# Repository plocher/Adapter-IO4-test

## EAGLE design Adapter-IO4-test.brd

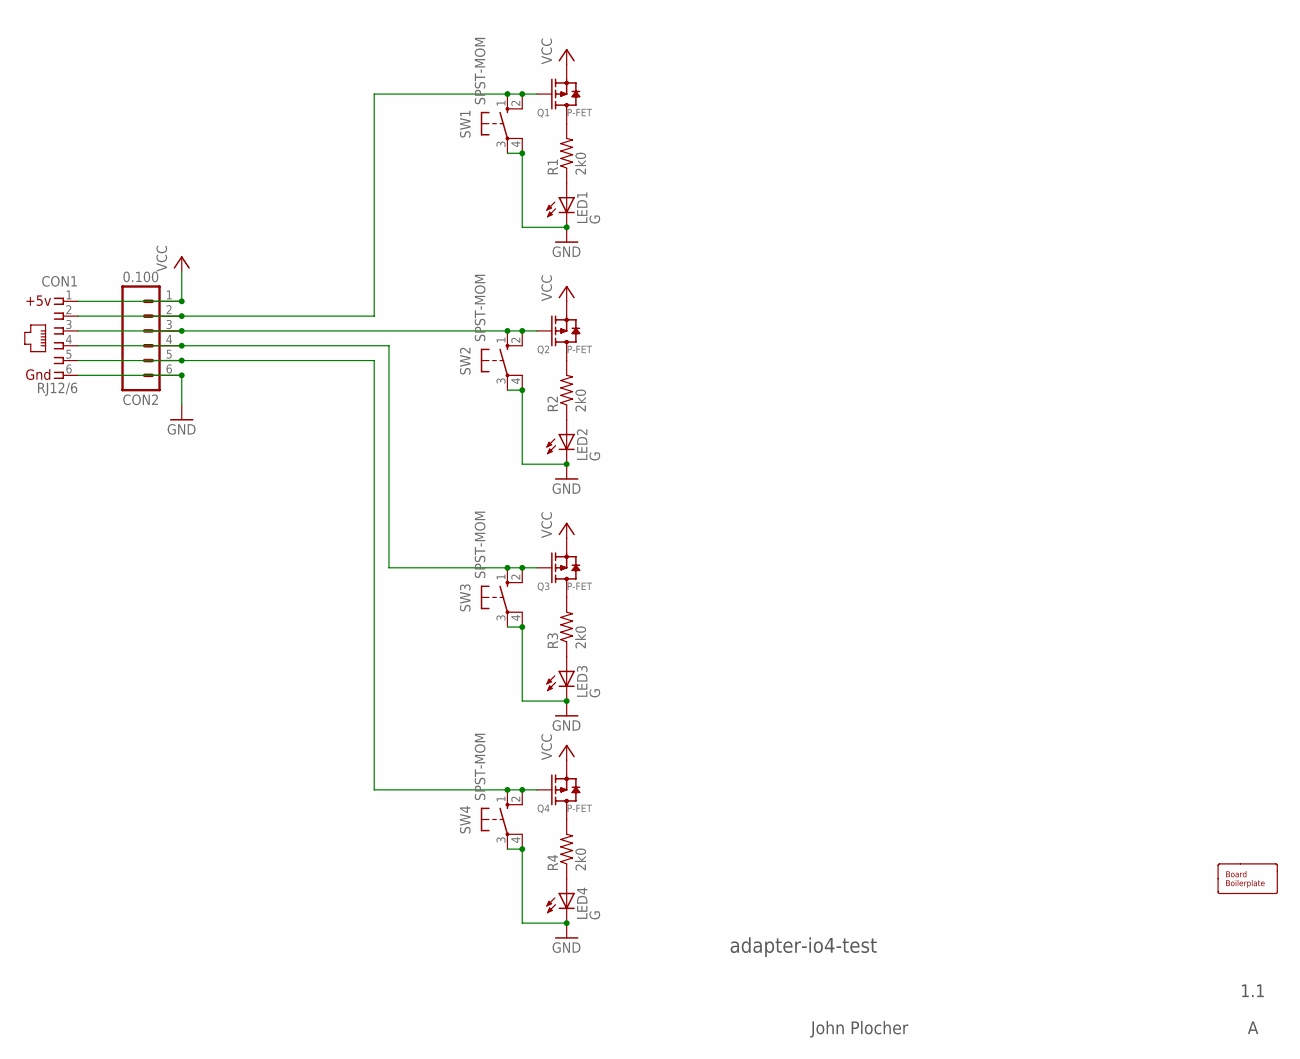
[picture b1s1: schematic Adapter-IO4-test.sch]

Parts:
BOARD1: BOARD50X50-NOHOLES; BOARD-SEEED5X5-NOHOLES
CON1: RJ12/6; RJ25-INVERTED
CON2: 0.100; 1X06_LOCK
LED1, LED2, LED3, LED4: G; 0603-LED
Q1, Q2, Q3, Q4: P-FET; SOT23-3
R1, R2, R3, R4: 2k0; 0603-RES
SW1, SW2, SW3, SW4: SPST-MOM; B3F-10XX

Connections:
GND: CON1.6, CON2.6, LED1.C, LED2.C, LED3.C, LED4.C, SW1.3, SW1.4 (P1), SW2.3, SW2.4 (P1), SW3.3, SW3.4 (P1), SW4.3, SW4.4 (P1)
unnamed: Q1.3 (D), R1.2
unnamed: LED1.A, R1.1
unnamed: Q2.3 (D), R2.2
unnamed: LED2.A, R2.1
unnamed: Q3.3 (D), R3.2
unnamed: LED3.A, R3.1
unnamed: CON1.2, CON2.2, Q1.1 (G), SW1.1 (S), SW1.2 (S1)
unnamed: CON1.3, CON2.3, Q2.1 (G), SW2.1 (S), SW2.2 (S1)
unnamed: CON1.4, CON2.4, Q3.1 (G), SW3.1 (S), SW3.2 (S1)
unnamed: CON1.5, CON2.5, Q4.1 (G), SW4.1 (S), SW4.2 (S1)
unnamed: Q4.3 (D), R4.2
unnamed: LED4.A, R4.1
VCC: CON1.1, CON2.1, Q1.2 (S), Q2.2 (S), Q3.2 (S), Q4.2 (S)

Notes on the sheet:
1.1
John Plocher

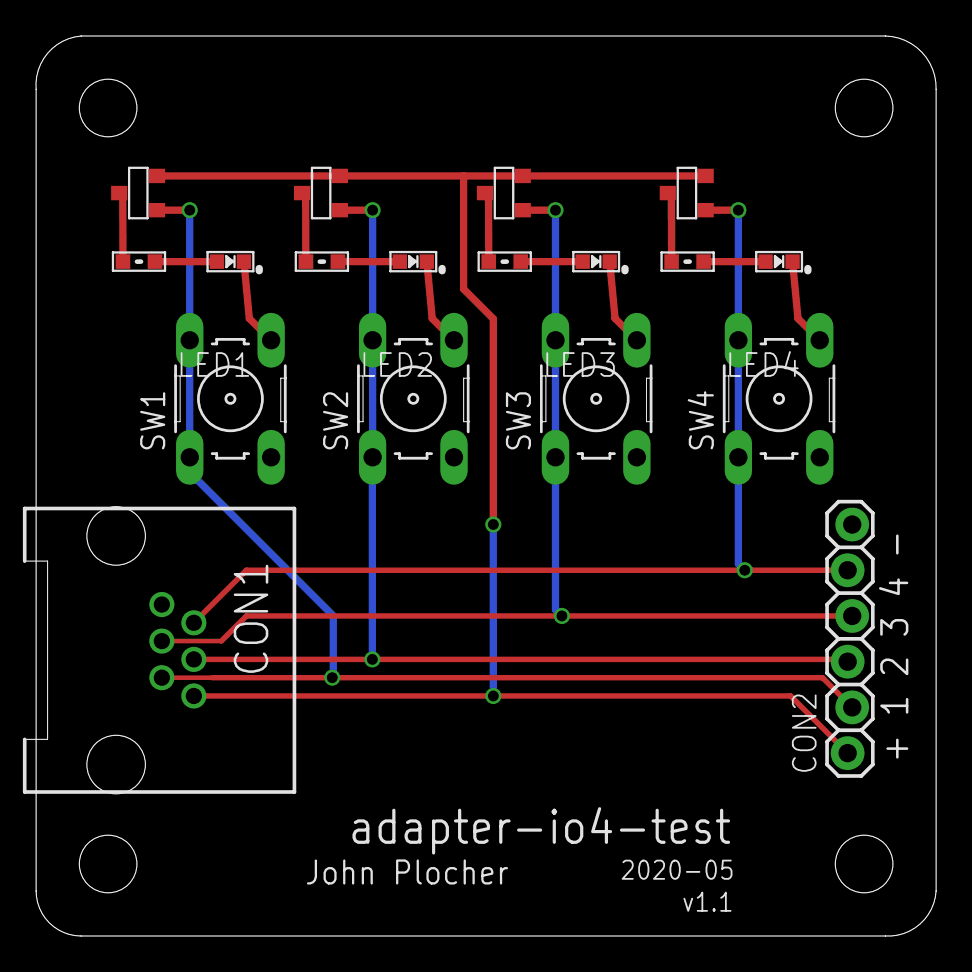
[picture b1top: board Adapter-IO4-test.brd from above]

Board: 2 copper layers, 50.0 x 50.0 mm, 19 parts (0 on the bottom side), 14 nets.

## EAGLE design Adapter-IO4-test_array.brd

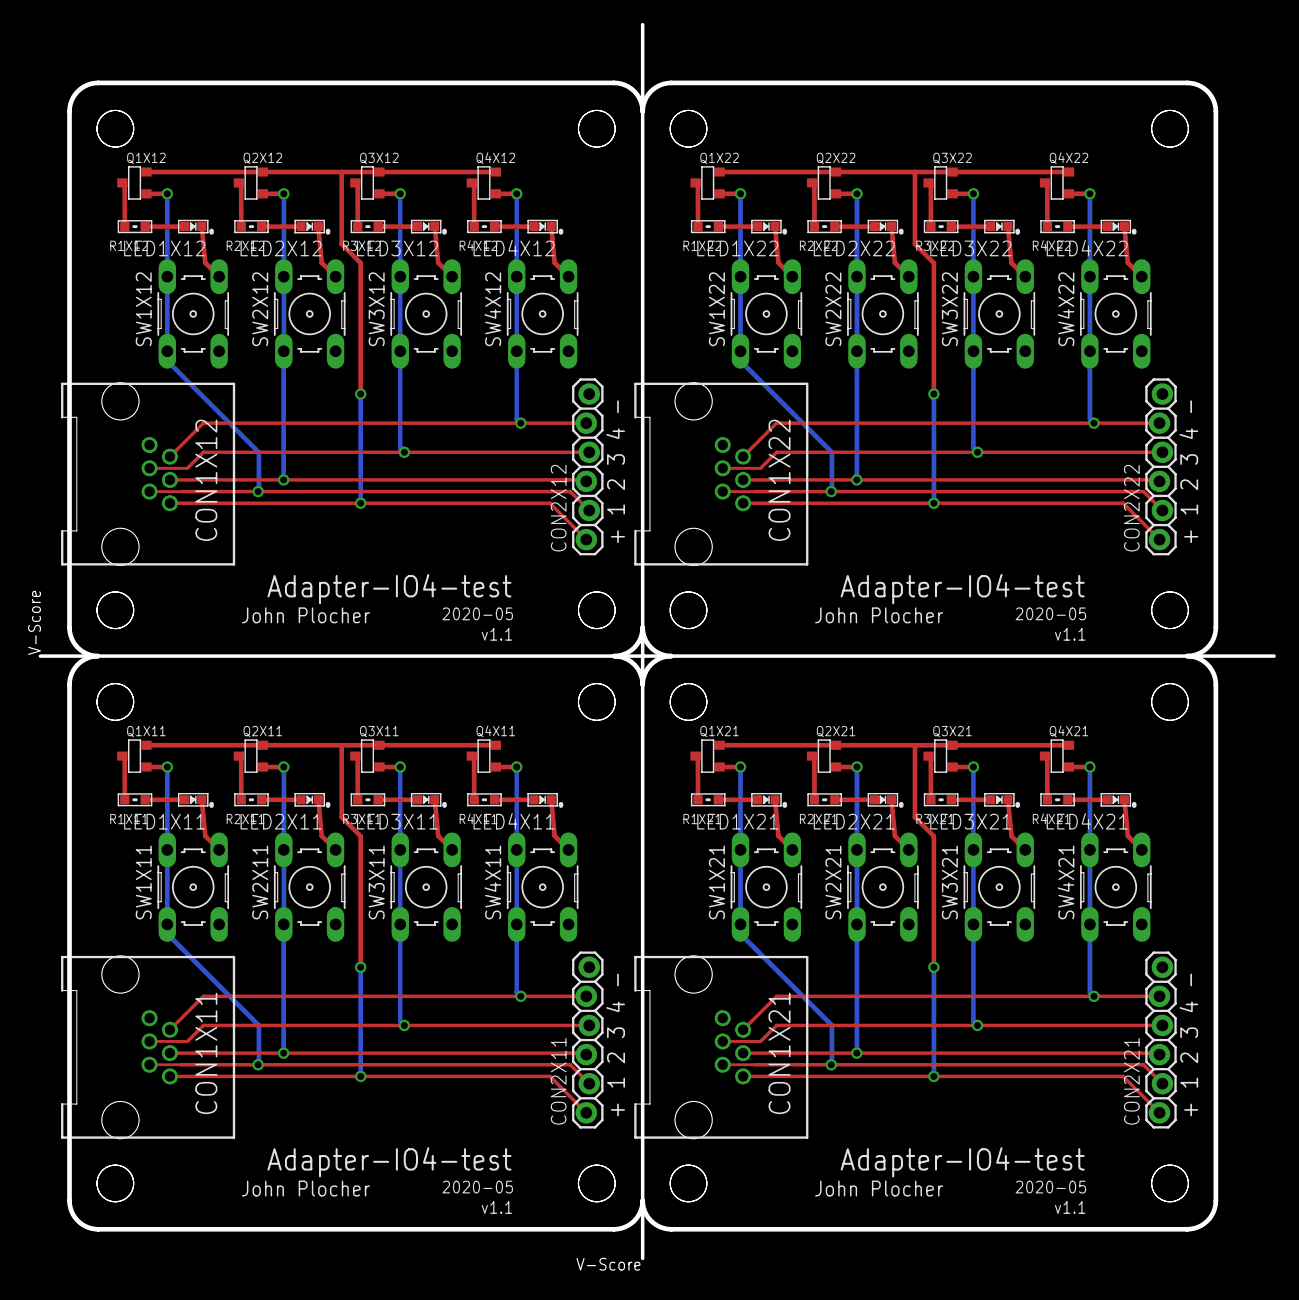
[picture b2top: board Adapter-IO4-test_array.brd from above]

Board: 2 copper layers, 108.9 x 109.0 mm, 72 parts (0 on the bottom side), 56 nets.

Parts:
CON1X11, CON1X12, CON1X21, CON1X22: RJ12/6; RJ25-INVERTED
CON2X11, CON2X12, CON2X21, CON2X22: 0.100; 1X06_LOCK
LED1X11, LED1X12, LED1X21, LED1X22, LED2X11, LED2X12, LED2X21, LED2X22, LED3X11, LED3X12, LED3X21, LED3X22, LED4X11, LED4X12, LED4X21, LED4X22: G; 0603-LED
Q1X11, Q1X12, Q1X21, Q1X22, Q2X11, Q2X12, Q2X21, Q2X22, Q3X11, Q3X12, Q3X21, Q3X22, Q4X11, Q4X12, Q4X21, Q4X22: p-fet; SOT23-3
R1X11, R1X12, R1X21, R1X22, R2X11, R2X12, R2X21, R2X22, R3X11, R3X12, R3X21, R3X22, R4X11, R4X12, R4X21, R4X22: 2k0; 0603-RES
SW1X11, SW1X12, SW1X21, SW1X22, SW2X11, SW2X12, SW2X21, SW2X22, SW3X11, SW3X12, SW3X21, SW3X22, SW4X11, SW4X12, SW4X21, SW4X22: SPST-MOM; B3F-10XX

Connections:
GNDX11: CON1X11.6, CON2X11.6, LED1X11.C, LED2X11.C, LED3X11.C, LED4X11.C, SW1X11.3, SW1X11.4, SW2X11.3, SW2X11.4, SW3X11.3, SW3X11.4, SW4X11.3, SW4X11.4
GNDX12: CON1X12.6, CON2X12.6, LED1X12.C, LED2X12.C, LED3X12.C, LED4X12.C, SW1X12.3, SW1X12.4, SW2X12.3, SW2X12.4, SW3X12.3, SW3X12.4, SW4X12.3, SW4X12.4
GNDX21: CON1X21.6, CON2X21.6, LED1X21.C, LED2X21.C, LED3X21.C, LED4X21.C, SW1X21.3, SW1X21.4, SW2X21.3, SW2X21.4, SW3X21.3, SW3X21.4, SW4X21.3, SW4X21.4
GNDX22: CON1X22.6, CON2X22.6, LED1X22.C, LED2X22.C, LED3X22.C, LED4X22.C, SW1X22.3, SW1X22.4, SW2X22.3, SW2X22.4, SW3X22.3, SW3X22.4, SW4X22.3, SW4X22.4
unnamed: Q1X11.3, R1X11.2
unnamed: Q1X12.3, R1X12.2
unnamed: Q1X21.3, R1X21.2
unnamed: Q1X22.3, R1X22.2
unnamed: LED1X11.A, R1X11.1
unnamed: LED1X12.A, R1X12.1
unnamed: LED1X21.A, R1X21.1
unnamed: LED1X22.A, R1X22.1
unnamed: Q2X11.3, R2X11.2
unnamed: Q2X12.3, R2X12.2
unnamed: Q2X21.3, R2X21.2
unnamed: Q2X22.3, R2X22.2
unnamed: LED2X11.A, R2X11.1
unnamed: LED2X12.A, R2X12.1
unnamed: LED2X21.A, R2X21.1
unnamed: LED2X22.A, R2X22.1
unnamed: Q3X11.3, R3X11.2
unnamed: Q3X12.3, R3X12.2
unnamed: Q3X21.3, R3X21.2
unnamed: Q3X22.3, R3X22.2
unnamed: LED3X11.A, R3X11.1
unnamed: LED3X12.A, R3X12.1
unnamed: LED3X21.A, R3X21.1
unnamed: LED3X22.A, R3X22.1
unnamed: CON1X11.2, CON2X11.2, Q1X11.1, SW1X11.1, SW1X11.2
unnamed: CON1X12.2, CON2X12.2, Q1X12.1, SW1X12.1, SW1X12.2
unnamed: CON1X21.2, CON2X21.2, Q1X21.1, SW1X21.1, SW1X21.2
unnamed: CON1X22.2, CON2X22.2, Q1X22.1, SW1X22.1, SW1X22.2
unnamed: CON1X11.3, CON2X11.3, Q2X11.1, SW2X11.1, SW2X11.2
unnamed: CON1X12.3, CON2X12.3, Q2X12.1, SW2X12.1, SW2X12.2
unnamed: CON1X21.3, CON2X21.3, Q2X21.1, SW2X21.1, SW2X21.2
unnamed: CON1X22.3, CON2X22.3, Q2X22.1, SW2X22.1, SW2X22.2
unnamed: CON1X11.4, CON2X11.4, Q3X11.1, SW3X11.1, SW3X11.2
unnamed: CON1X12.4, CON2X12.4, Q3X12.1, SW3X12.1, SW3X12.2
unnamed: CON1X21.4, CON2X21.4, Q3X21.1, SW3X21.1, SW3X21.2
unnamed: CON1X22.4, CON2X22.4, Q3X22.1, SW3X22.1, SW3X22.2
unnamed: CON1X11.5, CON2X11.5, Q4X11.1, SW4X11.1, SW4X11.2
unnamed: CON1X12.5, CON2X12.5, Q4X12.1, SW4X12.1, SW4X12.2
unnamed: CON1X21.5, CON2X21.5, Q4X21.1, SW4X21.1, SW4X21.2
unnamed: CON1X22.5, CON2X22.5, Q4X22.1, SW4X22.1, SW4X22.2
unnamed: Q4X11.3, R4X11.2
unnamed: Q4X12.3, R4X12.2
unnamed: Q4X21.3, R4X21.2
unnamed: Q4X22.3, R4X22.2
unnamed: LED4X11.A, R4X11.1
unnamed: LED4X12.A, R4X12.1
unnamed: LED4X21.A, R4X21.1
unnamed: LED4X22.A, R4X22.1
VCCX11: CON1X11.1, CON2X11.1, Q1X11.2, Q2X11.2, Q3X11.2, Q4X11.2
VCCX12: CON1X12.1, CON2X12.1, Q1X12.2, Q2X12.2, Q3X12.2, Q4X12.2
VCCX21: CON1X21.1, CON2X21.1, Q1X21.2, Q2X21.2, Q3X21.2, Q4X21.2
VCCX22: CON1X22.1, CON2X22.1, Q1X22.2, Q2X22.2, Q3X22.2, Q4X22.2

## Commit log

2020-01-22 breakout with buttons and leds
2020-01-22 added mounting holes
2020-05-04 updated tags
2020-05-04 simplified design
2020-07-16 Updated INFO
2020-07-30 added values to schematic
2020-07-30 bumped sch version
2020-08-03 added value G to LEDs
2020-08-04 array needed R and Q values as well
2020-08-05 fixed SPCoast lbr part orientation
2020-10-05 added values for connectors
2020-10-06 normalized values
